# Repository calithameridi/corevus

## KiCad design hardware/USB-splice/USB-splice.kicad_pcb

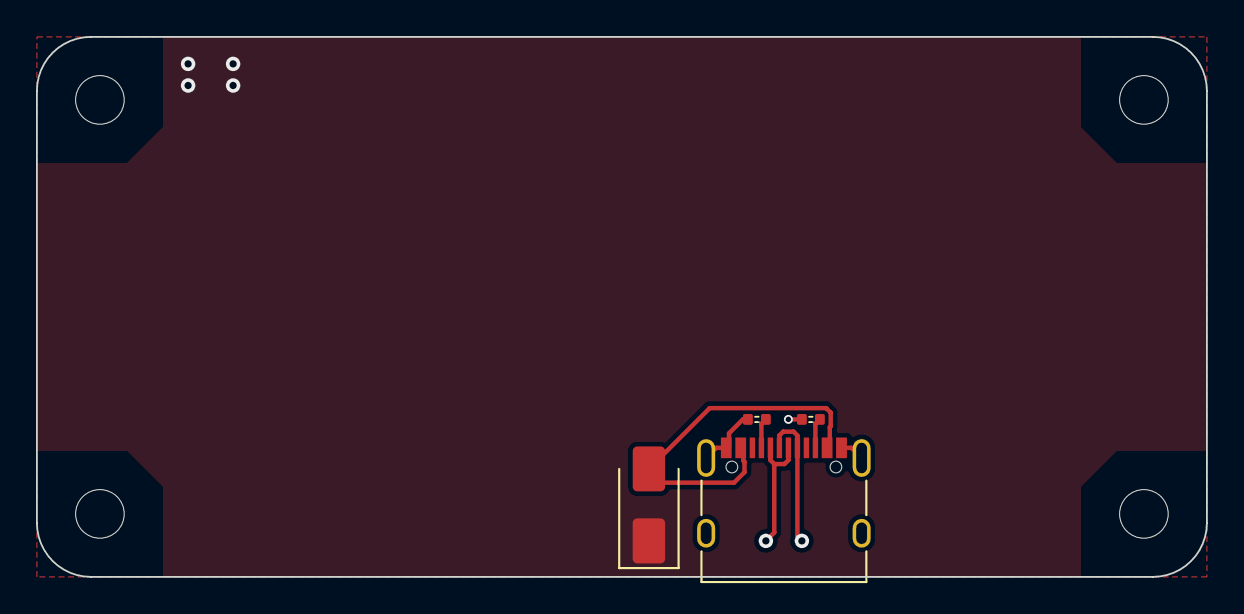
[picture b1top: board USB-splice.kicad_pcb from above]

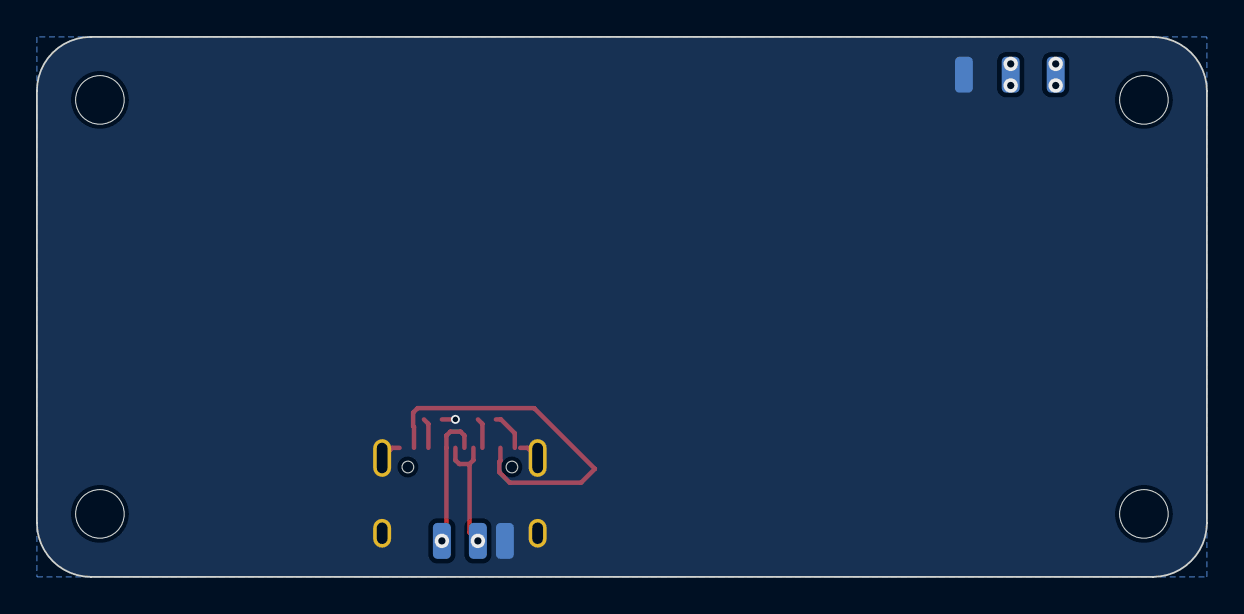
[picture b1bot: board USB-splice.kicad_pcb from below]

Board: 2 copper layers, 65.0 x 30.0 mm, 14 parts (6 on the bottom side), 7 nets.

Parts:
D1: SS54; D_SMA
H1, H2, H3, H4: MountingHole; MountingHole_2.7mm_M2.5
J1: USB 2.0; USB_Type-C_16p
R1, R2: 5.1kΩ; 0402R
T1, T2: 5V; LGA_Land_2mm
T3, T6: Gnd; LGA_Land_2mm
T4: D-; LGA_Land_2mm
T5: D+; LGA_Land_2mm

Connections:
+5V: D1.1 (K), T1.1, T2.1
GND: J1.A1 (GND), J1.A12 (GND), J1.B1 (GND), J1.B12 (GND), J1.S1 (SHIELD), R1.1, R2.1, T3.1, T6.1
unnamed: D1.2 (A), J1.A4 (VBUS), J1.A9 (VBUS), J1.B4 (VBUS), J1.B9 (VBUS)
unnamed: J1.A5 (CC1), R1.2
unnamed: J1.B5 (CC2), R2.2
unnamed: J1.A6 (D+), J1.B6 (D+), T5.1
unnamed: J1.A7 (D-), J1.B7 (D-), T4.1

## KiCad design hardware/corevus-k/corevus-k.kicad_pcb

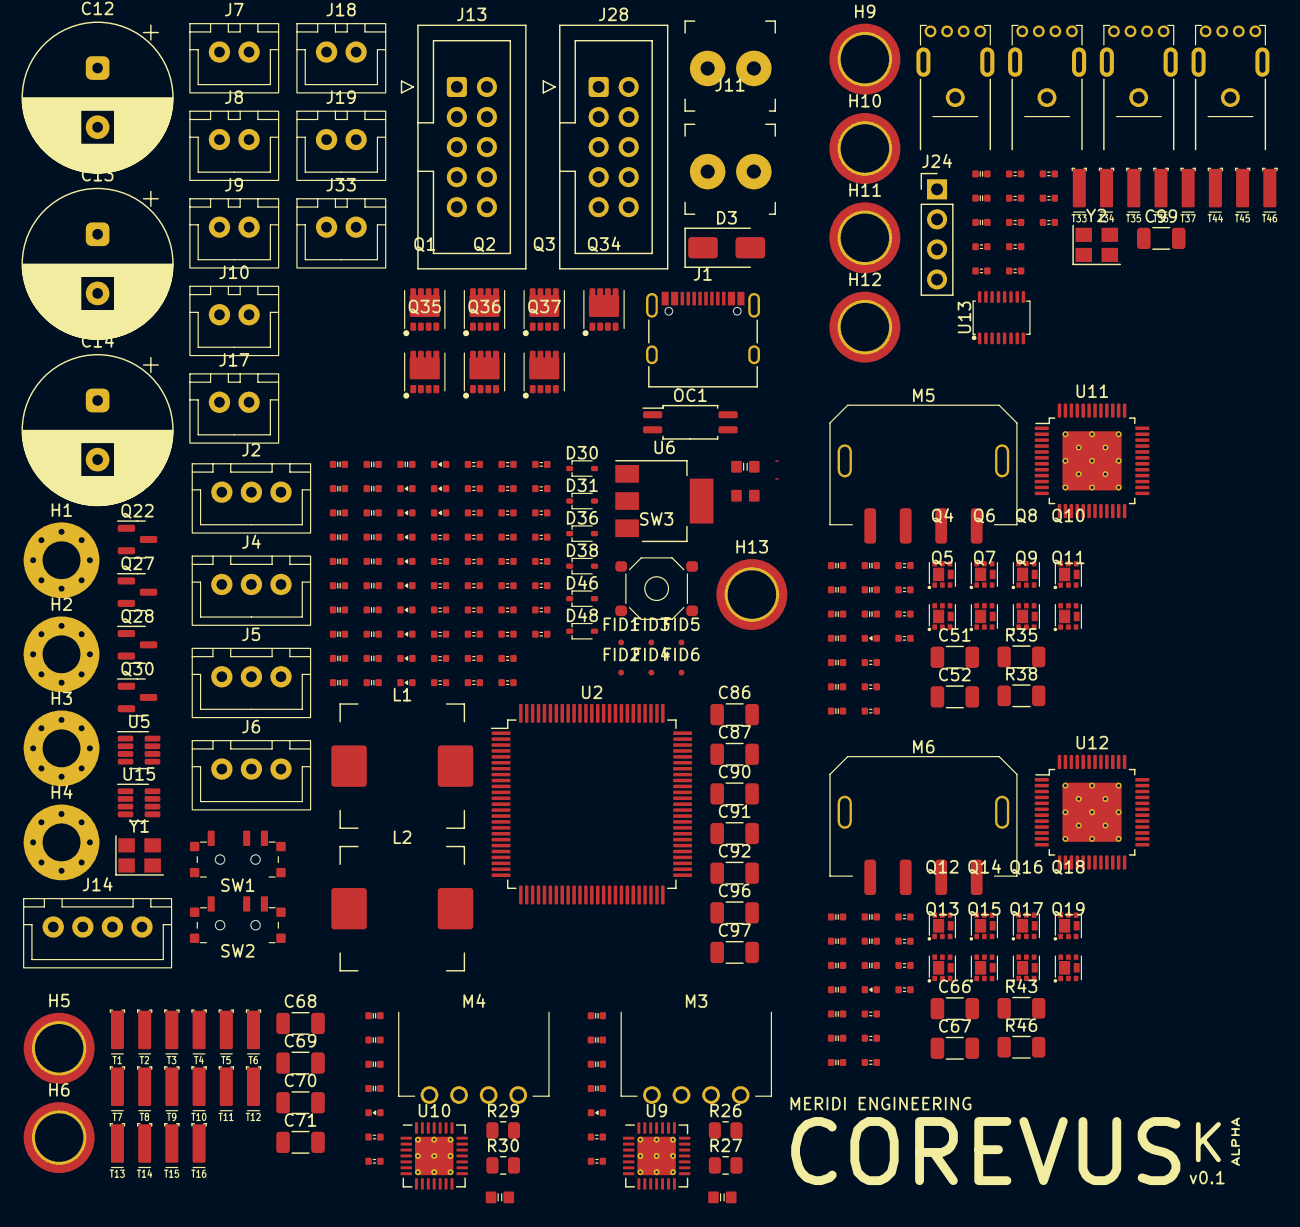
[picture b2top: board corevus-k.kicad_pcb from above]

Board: 4 copper layers, 283 parts (0 on the bottom side), 186 nets, no tracks yet.

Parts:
C1, C2: 15pF; 0402C
C3, C4: 2.2μF; 0402C
C5: 100nF 50V; 0402C
C6, C7, C8, C9, C29, C34, C41, C42, C43, C45, C56, C57, C58, C60, C76, C88, C93, C94, C98: 1μF; 0402C
C11: 10μF; 0603C
C12, C13, C14: 470μF 63V; CP_Radial_D12.5mm_P5.00mm
C28, C33, C38, C79, C80, C81, C82, C83, C84, C85, C89, C95: 100nF; 0402C
C30, C35, C39, C54: 100nF 16V; 0402C
C31, C36: 22nF 50V; 0402C
C32, C37: 1μF 50V; 0603C
C40, C55: 47nF 100V; 0402C
C47, C48, C49, C50, C62, C63, C64, C65: 220nF; 0402C
C51, C52, C66, C67: 1μF 100V; C_1206_3216Metric
C68, C69, C70, C71: 1μF 63V; C_1206_3216Metric
C86, C87, C92: 10μF 50V; C_1206_3216Metric
C90, C91: 22μF 25V; C_1206_3216Metric
C96, C97: 22μF 10V; C_1206_3216Metric
C99: 22μF; C_1206_3216Metric
D1, D2, D4, D5, D6, D7, D8, D19, D20, D23, D24, D28, D29, D32, D34, D49: Red; 0402LED
D3: SS54; D_SMA
D30, D31, D36, D38: 1N4148; D_SOD-323
D46, D48: 1N5819; D_SOD-323
FB1: GZ1608; 0603
FID1, FID2, FID3, FID4, FID5, FID6: Fiducial; Fiducial_0.5mm_Mask1mm
H1, H2, H3, H4: MountingHole; MountingHole_3.2mm_M3_Pad_Via
H5: V_{M}; M3_M2.5_PCB_Nut
H6: Gnd; M3_M2.5_PCB_Nut
H9, H10, H11, H12: M2.5; M3_M2.5_PCB_Nut
H13: Back; M3_M2.5_PCB_Nut
J1: USB 2.0; USB_Type-C_16p
J2: JST XH; JST_XH_1x03
J3, J11: ScrewTerminal; DB125-3.81-2P
J4, J5, J6: XH; JST_XH_1x03
J7, J8, J9, J10, J17, J18, J19, J33: JST XH; JST_XH_1x02
J12, J15, J16, J20: USB_A; Jing_USB-A_906-761
J13: EXP1; IDC-Header_2x05_P2.54mm_Vertical
J14: JST XH; JST_XH_1x04
J24: Conn_01x05_Pin; PinHeader_1x04_P2.54mm_Vertical
J28: EXP2; IDC-Header_2x05_P2.54mm_Vertical
L1, L2: 10μH; CJiang_FXL1040
M3, M4: JST XH; JST_XH_1x04-Side
M5, M6: Micro-Fit 3.0; XKB_X3025WRS-04C
NT1, NT2: NetTie_2; NetTie-2_SMD_Pad0.1mm
OC1: PC3H7; SOP-4_4.4x2.6mm_P1.27mm
Q1, Q2, Q3, Q34, Q35, Q36, Q37: 60N03F; MOSFET_DFN8
Q4, Q5, Q6, Q7, Q8, Q9, Q10, Q11, Q12, Q13, Q14, Q15, Q16, Q17, Q18, Q19: DMT6016LFDF
Q22, Q27, Q28, Q30: AO3400; SOT-23
R1, R19, R67, R71, R72, R73, R83, R102, R105, R106, R107: 10kΩ; 0402R
R2, R10, R12, R13, R14, R96, R98, R99, R101, R103: 1kΩ; 0402R
R4, R5, R69, R70, R75, R76, R77, R78, R79, R80, R81, R82: 33Ω; 0402R
R6, R7: 5.1kΩ; 0402R
R9: 200kΩ; 0402R
R11: 100kΩ; 0402R
R15, R16, R17, R18, R39, R47, R48, R49, R54, R93: 4.7kΩ; 0402R
R26, R27, R29, R30: 100mΩ; R_0805_2012Metric
R32, R40: 2.2Ω; 0402R
R33, R34, R36, R37, R41, R42, R44, R45: 47Ω; 0402R
R35, R38, R43, R46: 33mΩ; R_1206_3216Metric
R52, R55, R104: 200Ω; 0402R
R92: 330Ω; 0402R
R94: 1.5kΩ; 0402R
R95: 8.2kΩ; 0402R
SW1, SW2: SW_SPDT; MSS12C02-LS
SW3: SPST; XKB_TS-1187A
T1: V_{SA}; LGA_Spring
T2: SClk; LGA_Spring
T3, T35: Gnd; LGA_Spring
T4: MOSI; LGA_Spring
T5: MISO; LGA_Spring
T6: V_{CC}IO; LGA_Spring
T7, T8, T9, T10, T11, T12, T13, T14, T15, T16: TestPoint; LGA_Spring
T33, T34: 5V; LGA_Spring
T36: TXD; LGA_Spring
T37: RXD; LGA_Spring
T44: Shield; LGA_Spring
T45: D+; LGA_Spring
T46: D-; LGA_Spring
U2: STM32F407VETx; LQFP-100_14x14mm_P0.5mm
U5, U15: RT8110B; TSOT-23-8
U6: AMS1117-3.3; SOT-223-3_TabPin2
U9, U10: TMC2208-LA; TMC220x
U11, U12: TMC5160A-TA; TMCx160
U13: SL2.1S
Y1: 12 MHz; Crystal_SMD_3225-4Pin_3.2x2.5mm
Y2: 12MHz; Crystal_SMD_3225-4Pin_3.2x2.5mm

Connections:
+3.3V: C11.1, C28.1, C33.1, C41.2, C56.2, C79.1, C80.1, C81.1, C82.1, C83.1, C84.1, C85.1, D19.2 (A), D20.2 (A), D23.2 (A), D24.2 (A), FB1.1, J4.3, J5.3, J6.3, R12.2, R19.1, R52.2, R55.2, R102.1, R104.2, R105.1, R106.1, R107.1, SW1.3 (C), T6.1, U2.6 (VBAT), U2.11 (VDD), U2.19 (VDD), U2.28 (VDD), U2.50 (VDD), U2.75 (VDD), U2.100 (VDD), U6.2 (VO), U9.9 (MS1), U9.10 (MS2), U9.15 (Vcc_IO), U10.9 (MS1), U10.10 (MS2), U10.15 (Vcc_IO), U11.20 (VCC_IO), U11.21 (SD_MODE), U11.22 (SPI_MODE), U12.20 (VCC_IO), U12.21 (SD_MODE), U12.22 (SPI_MODE)
+5V: C96.1, C97.1, C98.1, C99.1, D3.1 (K), J12.1 (VBUS), J13.10, J15.1 (VBUS), J16.1 (VBUS), J20.1 (VBUS), J24.1, J28.10, L2.2, R95.2, SW2.3 (C), T33.1, T34.1, U6.3 (VI), U13.7 (VDD5)
+12V: C45.2, C60.2, C90.1, C91.1, L1.2, R93.2, T1.1, U11.3 (12VOUT), U11.4 (VSA), U12.3 (12VOUT), U12.4 (VSA)
+24V: C12.1, C30.2, C32.2, C35.2, C37.2, C68.1, C69.1, C70.1, C71.1, C86.1, C87.1, C92.1, H5.1, J3.1, J11.1, Q35.5 (D), Q35.6 (D), Q35.7 (D), Q35.8 (D), Q37.5 (D), Q37.6 (D), Q37.7 (D), Q37.8 (D), SW2.1 (A), U5.7 (VIN), U9.22 (VS), U9.28 (VS), U10.22 (VS), U10.28 (VS), U15.7 (VIN)
/BOOT0: D1.2 (A), R1.1, SW1.2 (B), U2.94 (BOOT0)
/E0: D6.1 (K), J4.1
/E1: D7.1 (K), J5.1
/E2: D8.1 (K), J6.1
/F0: D5.2 (A), J14.4, R67.1
/F1_V+: D38.1 (K), J33.1
/F2_Gate: D28.2 (A), Q22.1 (G), R71.1
/F2_V+: D30.1 (K), J17.1
/F3_Gate: D29.2 (A), Q27.1 (G), R72.1
/F3_V+: D31.1 (K), J18.1
/F4_Gate: D32.2 (A), Q28.1 (G), R73.1
/F4_V+: D36.1 (K), J19.1
/F6_Gate: D34.2 (A), Q30.1 (G), R83.1
/H0_Gate: D4.2 (A), Q3.4 (G)
/HB_Gate: D2.2 (A), Q1.4 (G), Q2.4 (G)
/Motor 0 (TMCx160)/CA1: C47.1, U11.42 (CA1)
/Motor 0 (TMCx160)/CA2: C49.2, U11.35 (CA2)
/Motor 0 (TMCx160)/CB1: C48.1, U11.2 (CB1)
/Motor 0 (TMCx160)/CB2: C50.2, U11.43 (CB2)
/Motor 0 (TMCx160)/HA1: Q6.3 (G), U11.41 (HA1)
/Motor 0 (TMCx160)/HA2: Q4.3 (G), U11.36 (HA2)
/Motor 0 (TMCx160)/HB1: Q10.3 (G), U11.1 (HB1)
/Motor 0 (TMCx160)/HB2: Q8.3 (G), U11.44 (HB2)
/Motor 0 (TMCx160)/LA1: Q7.3 (G), U11.39 (LA1)
/Motor 0 (TMCx160)/LA2: Q5.3 (G), U11.38 (LA2)
/Motor 0 (TMCx160)/LB1: Q11.3 (G), U11.47 (LB1)
/Motor 0 (TMCx160)/LB2: Q9.3 (G), U11.46 (LB2)
/Motor 0 (TMCx160)/Motor_A1: C47.2, M5.3, Q6.4 (S), Q6.7 (S), Q7.1 (D), Q7.2 (D), Q7.5 (D), Q7.6 (D), Q7.8 (D), U11.40 (BMA1)
/Motor 0 (TMCx160)/Motor_A2: C49.1, M5.4, Q4.4 (S), Q4.7 (S), Q5.1 (D), Q5.2 (D), Q5.5 (D), Q5.6 (D), Q5.8 (D), U11.37 (BMA2)
/Motor 0 (TMCx160)/Motor_B1: C48.2, M5.1, Q10.4 (S), Q10.7 (S), Q11.1 (D), Q11.2 (D), Q11.5 (D), Q11.6 (D), Q11.8 (D), U11.48 (BMB1)
/Motor 0 (TMCx160)/Motor_B2: C50.1, M5.2 (-), Q8.4 (S), Q8.7 (S), Q9.1 (D), Q9.2 (D), Q9.5 (D), Q9.6 (D), Q9.8 (D), U11.45 (BMB2)
/Motor 0 (TMCx160)/SRAH: R33.2, U11.8 (SRAH)
/Motor 0 (TMCx160)/SRAL: R34.2, U11.7 (SRAL)
/Motor 0 (TMCx160)/SRBH: R36.2, U11.9 (SRBH)
/Motor 0 (TMCx160)/SRBL: R37.2, U11.10 (SRBL)
/Motor 1 (TMCx160)/CA1: C62.1, U12.42 (CA1)
/Motor 1 (TMCx160)/CA2: C64.2, U12.35 (CA2)
/Motor 1 (TMCx160)/CB1: C63.1, U12.2 (CB1)
/Motor 1 (TMCx160)/CB2: C65.2, U12.43 (CB2)
/Motor 1 (TMCx160)/HA1: Q14.3 (G), U12.41 (HA1)
/Motor 1 (TMCx160)/HA2: Q12.3 (G), U12.36 (HA2)
/Motor 1 (TMCx160)/HB1: Q18.3 (G), U12.1 (HB1)
/Motor 1 (TMCx160)/HB2: Q16.3 (G), U12.44 (HB2)
/Motor 1 (TMCx160)/LA1: Q15.3 (G), U12.39 (LA1)
/Motor 1 (TMCx160)/LA2: Q13.3 (G), U12.38 (LA2)
/Motor 1 (TMCx160)/LB1: Q19.3 (G), U12.47 (LB1)
/Motor 1 (TMCx160)/LB2: Q17.3 (G), U12.46 (LB2)
/Motor 1 (TMCx160)/Motor_A1: C62.2, M6.3, Q14.4 (S), Q14.7 (S), Q15.1 (D), Q15.2 (D), Q15.5 (D), Q15.6 (D), Q15.8 (D), U12.40 (BMA1)
/Motor 1 (TMCx160)/Motor_A2: C64.1, M6.4, Q12.4 (S), Q12.7 (S), Q13.1 (D), Q13.2 (D), Q13.5 (D), Q13.6 (D), Q13.8 (D), U12.37 (BMA2)
/Motor 1 (TMCx160)/Motor_B1: C63.2, M6.1, Q18.4 (S), Q18.7 (S), Q19.1 (D), Q19.2 (D), Q19.5 (D), Q19.6 (D), Q19.8 (D), U12.48 (BMB1)
/Motor 1 (TMCx160)/Motor_B2: C65.1, M6.2 (-), Q16.4 (S), Q16.7 (S), Q17.1 (D), Q17.2 (D), Q17.5 (D), Q17.6 (D), Q17.8 (D), U12.45 (BMB2)
/Motor 1 (TMCx160)/SRAH: R41.2, U12.8 (SRAH)
/Motor 1 (TMCx160)/SRAL: R42.2, U12.7 (SRAL)
/Motor 1 (TMCx160)/SRBH: R44.2, U12.9 (SRBH)
/Motor 1 (TMCx160)/SRBL: R45.2, U12.10 (SRBL)
/Motor 2 (TMC2208)/A1: M3.2 (-), U9.24 (OA1)
/Motor 2 (TMC2208)/A2: M3.1, U9.21 (OA2)
/Motor 2 (TMC2208)/B1: M3.3, U9.26 (OB1)
/Motor 2 (TMC2208)/B2: M3.4, U9.1 (OB2)
/Motor 2 (TMC2208)/BRA: R26.1, U9.23 (BRA)
/Motor 2 (TMC2208)/BRB: R27.1, U9.27 (BRB)
/Motor 3 (TMC2208)/A1: M4.2 (-), U10.24 (OA1)
/Motor 3 (TMC2208)/A2: M4.1, U10.21 (OA2)
/Motor 3 (TMC2208)/B1: M4.3, U10.26 (OB1)
/Motor 3 (TMC2208)/B2: M4.4, U10.1 (OB2)
/Motor 3 (TMC2208)/BRA: R29.1, U10.23 (BRA)
/Motor 3 (TMC2208)/BRB: R30.1, U10.27 (BRB)
/Pi Zero + USB Hub/D1+: R75.2, U13.4 (DP1)
/Pi Zero + USB Hub/D1+': J12.3 (D+), R75.1
/Pi Zero + USB Hub/D1-: R76.2, U13.3 (DM1)
/Pi Zero + USB Hub/D1-': J12.2 (D-), R76.1
/Pi Zero + USB Hub/D2+: R77.2, U13.2 (DP2)
/Pi Zero + USB Hub/D2+': J15.3 (D+), R77.1
/Pi Zero + USB Hub/D2-: R78.2, U13.1 (DM2)
/Pi Zero + USB Hub/D2-': J15.2 (D-), R78.1
/Pi Zero + USB Hub/D3+: R79.2, U13.16 (DP3)
/Pi Zero + USB Hub/D3+': J16.3 (D+), R79.1
/Pi Zero + USB Hub/D3-: R80.2, U13.15 (DM3)
/Pi Zero + USB Hub/D3-': J16.2 (D-), R80.1
/Pi Zero + USB Hub/D4+: R81.2, U13.14 (DP4)
/Pi Zero + USB Hub/D4+': J20.3 (D+), R81.1
/Pi Zero + USB Hub/D4-: R82.2, U13.13 (DM4)
/Pi Zero + USB Hub/D4-': J20.2 (D-), R82.1
/Pi Zero + USB Hub/DU+: R69.1, U13.6 (UDP)
/Pi Zero + USB Hub/DU+': R69.2, T45.1
/Pi Zero + USB Hub/DU-: R70.1, U13.5 (UDM)
/Pi Zero + USB Hub/DU-': R70.2, T46.1
/Probe: OC1.3, R11.1, R96.2
/SPI1_MISO: T5.1, U11.16 (SDO/CFG0), U12.16 (SDO/CFG0)
/SPI1_MOSI: T4.1, U11.15 (SDI/CFG1), U12.15 (SDI/CFG1)
/SPI1_SCK: T2.1, U11.14 (SCK/CFG2), U12.14 (SCK/CFG2)
/T0: C6.2, J8.2, R15.1
/T1: C7.2, J7.2, R16.1
/T2: C8.2, J9.2, R17.1
/T3: C9.2, J10.2, R18.1
/USART2_RX: J24.3, T36.1
/USART2_TX: J24.4, T37.1
/_{M0}~En: R99.2, R107.2, U12.28 (~DRV_EN)
/_{M2}~En: R101.2, R102.2, U9.2 (~En)
/_{M3}~En: R103.2, R105.2, U10.2 (~En)
/_{M4}~En: R98.2, R106.2, U11.28 (~DRV_EN)
GND: C1.1, C2.1, C3.2, C4.2, C5.2, C11.2, C12.2, C13.2, C14.2, C28.2, C29.1, C32.1, C33.2, C34.1, C37.1, C38.2, C41.1, C42.1, C43.1, C45.1, C51.2, C52.2, C56.1, C57.1, C58.1, C60.1, C66.2, C67.2, C68.2, C69.2, C70.2, C71.2, C76.2, C79.2, C80.2, C81.2, C82.2, C83.2, C84.2, C85.2, C86.2, C87.2, C88.2, C90.2, C91.2, C92.2, C93.2, C94.2, C96.2, C97.2, C98.2, C99.2, D49.1 (K), H6.1, H9.1, H10.1, H11.1, H12.1, J1.A1 (GND), J1.A12 (GND), J1.B1 (GND), J1.B12 (GND), J1.S1 (SHIELD), J2.2, J4.2, J5.2, J6.2, J12.4 (GND), J12.5 (Shield), J13.9, J14.2, J15.4 (GND), J15.5 (Shield), J16.4 (GND), J16.5 (Shield), J20.4 (GND), J20.5 (Shield), J24.2, J28.9, NT1.1, OC1.2, Q1.1 (S), Q1.2 (S), Q1.3 (S), Q2.1 (S), Q2.2 (S), Q2.3 (S), Q3.1 (S), Q3.2 (S), Q3.3 (S), Q22.2 (S), Q27.2 (S), Q28.2 (S), Q30.2 (S), Q34.1 (S), Q34.2 (S), Q34.3 (S), Q36.1 (S), Q36.2 (S), Q36.3 (S), R1.2, R2.1, R6.1, R7.1, R9.2, R11.2, R13.2, R14.2, R26.2, R27.2, R29.2, R30.2, R34.1, R35.2, R37.1, R38.2, R39.2, R42.1, R43.2, R45.1, R46.2, R47.2, R48.2, R49.2, R54.2, R67.2, R71.2, R72.2, R73.2, R83.2, R92.2, R94.2, SW1.1 (A), SW3.1, T3.1, T9.1, T10.1, T35.1, T44.1, U2.10 (VSS), U2.27 (VSS), U2.74 (VSS), U2.99 (VSS), U5.3 (GND), U6.1 (GND), U9.3 (Gnd), U9.7 (NC), U9.18 (Gnd), U9.20 (NC), U9.25 (NC), U9.29 (Pad), U10.3 (Gnd), U10.7 (NC), U10.18 (Gnd), U10.20 (NC), U10.25 (NC), U10.29 (Pad), U11.6 (GNDA), U11.11 (TST_MODE), U11.12 (CLK), U11.19 (GNDD), U11.30 (GNDD), U11.49 (EP), U12.6 (GNDA), U12.11 (TST_MODE), U12.12 (CLK), U12.19 (GNDD), U12.30 (GNDD), U12.49 (EP), U13.8 (VSS), U15.3 (GND), Y1.2, Y1.4, Y2.2, Y2.4
unnamed: D1.1 (K), R2.2
unnamed: D2.1 (K), R13.1
unnamed: D3.2 (A), J1.A4 (VBUS), J1.A9 (VBUS), J1.B4 (VBUS), J1.B9 (VBUS)
unnamed: D4.1 (K), R14.1
unnamed: D5.1 (K), R49.1
unnamed: D6.2 (A), R52.1
unnamed: D7.2 (A), R55.1
unnamed: D8.2 (A), R104.1
unnamed: D19.1 (K), R98.1
unnamed: D20.1 (K), R99.1
unnamed: D23.1 (K), R101.1
unnamed: D24.1 (K), R103.1
unnamed: D28.1 (K), R39.1
unnamed: D29.1 (K), R47.1
unnamed: D30.2 (A), J17.2, Q22.3 (D)
unnamed: D31.2 (A), J18.2, Q27.3 (D)
unnamed: D32.1 (K), R48.1
unnamed: D34.1 (K), R54.1
unnamed: D36.2 (A), J19.2, Q28.3 (D)
unnamed: D38.2 (A), J33.2, Q30.3 (D)
unnamed: C88.1, D46.2 (A), U15.1 (VCC)
unnamed: C89.1, D46.1 (K), U15.5 (BOOT)
unnamed: C94.1, D48.2 (A), U5.1 (VCC)
unnamed: C95.1, D48.1 (K), U5.5 (BOOT)
unnamed: D49.2 (A), R96.1
unnamed: J1.A5 (CC1), R6.2
unnamed: J1.B5 (CC2), R7.2
unnamed: J1.A6 (D+), J1.B6 (D+), R5.2
unnamed: J1.A7 (D-), J1.B7 (D-), R4.2
unnamed: C5.1, J2.1, SW2.2 (B)
unnamed: J2.3, R10.1
unnamed: J3.2, Q3.5 (D), Q3.6 (D), Q3.7 (D), Q3.8 (D)
unnamed: J11.2, Q1.5 (D), Q1.6 (D), Q1.7 (D), Q1.8 (D), Q2.5 (D), Q2.6 (D), Q2.7 (D), Q2.8 (D)
unnamed: OC1.1, R10.2
unnamed: OC1.4, R12.1
unnamed: Q5.4 (S), Q5.7 (S), Q7.4 (S), Q7.7 (S), R33.1, R35.1
unnamed: Q9.4 (S), Q9.7 (S), Q11.4 (S), Q11.7 (S), R36.1, R38.1
unnamed: Q13.4 (S), Q13.7 (S), Q15.4 (S), Q15.7 (S), R41.1, R43.1
unnamed: Q17.4 (S), Q17.7 (S), Q19.4 (S), Q19.7 (S), R44.1, R46.1
unnamed: Q34.4 (G), U15.2 (LGATE)
unnamed: Q35.4 (G), U15.4 (UGATE)
unnamed: Q36.4 (G), U5.2 (LGATE)
unnamed: Q37.4 (G), U5.4 (UGATE)
unnamed: C38.1, R19.2, SW3.2, U2.14 (NRST)
unnamed: R4.1, U2.70 (PA11)
unnamed: R5.1, U2.71 (PA12)
unnamed: C1.2, U2.12 (PH0), Y1.1
unnamed: C2.2, U2.13 (PH1), Y1.3
unnamed: C4.1, U2.49 (VCAP_1)
unnamed: C3.1, U2.73 (VCAP_2)
unnamed: NT2.2, U2.21 (VREF+)
unnamed: R94.1, R95.1, U5.8 (FB)
unnamed: C95.2, L2.1, Q36.5 (D), Q36.6 (D), Q36.7 (D), Q36.8 (D), Q37.1 (S), Q37.2 (S), Q37.3 (S), U5.6 (PHASE)
unnamed: C29.2, U9.8 (5VOut)
unnamed: C31.2, U9.5 (CPI)
unnamed: C31.1, U9.4 (CPO)
unnamed: C30.1, U9.6 (VCP)
unnamed: C34.2, U10.8 (5VOut)
unnamed: C36.2, U10.5 (CPI)
unnamed: C36.1, U10.4 (CPO)
unnamed: C35.1, U10.6 (VCP)
unnamed: C42.2, R32.1, U11.5 (5VOUT)
unnamed: C40.1, U11.32 (CPI)
unnamed: C40.2, U11.31 (CPO)
unnamed: C43.2, R32.2, U11.29 (VCC)
unnamed: C39.1, U11.34 (VCP)
unnamed: C57.2, R40.1, U12.5 (5VOUT)
unnamed: C55.1, U12.32 (CPI)
unnamed: C55.2, U12.31 (CPO)
unnamed: C58.2, R40.2, U12.29 (VCC)
unnamed: C54.1, U12.34 (VCP)
unnamed: C76.1, U13.10 (VDD18)
unnamed: C93.1, U13.9 (VDD33)
unnamed: U13.12 (XIN), Y2.1
unnamed: U13.11 (XOUT), Y2.3
unnamed: R92.1, R93.1, U15.8 (FB)
unnamed: C89.2, L1.1, Q34.5 (D), Q34.6 (D), Q34.7 (D), Q34.8 (D), Q35.1 (S), Q35.2 (S), Q35.3 (S), U15.6 (PHASE)
VDDA: FB1.2, NT2.1, R15.2, R16.2, R17.2, R18.2, U2.22 (VDDA)
VMB: C13.1, C14.1, C39.2, C51.1, C52.1, C54.2, C66.1, C67.1, Q4.1 (D), Q4.2 (D), Q4.5 (D), Q4.6 (D), Q4.8 (D), Q6.1 (D), Q6.2 (D), Q6.5 (D), Q6.6 (D), Q6.8 (D), Q8.1 (D), Q8.2 (D), Q8.5 (D), Q8.6 (D), Q8.8 (D), Q10.1 (D), Q10.2 (D), Q10.5 (D), Q10.6 (D), Q10.8 (D), Q12.1 (D), Q12.2 (D), Q12.5 (D), Q12.6 (D), Q12.8 (D), Q14.1 (D), Q14.2 (D), Q14.5 (D), Q14.6 (D), Q14.8 (D), Q16.1 (D), Q16.2 (D), Q16.5 (D), Q16.6 (D), Q16.8 (D), Q18.1 (D), Q18.2 (D), Q18.5 (D), Q18.6 (D), Q18.8 (D), R9.1, U11.33 (VS), U12.33 (VS)
VSSA: C6.1, C7.1, C8.1, C9.1, J7.1, J8.1, J9.1, J10.1, NT1.2, U2.20 (VSSA)

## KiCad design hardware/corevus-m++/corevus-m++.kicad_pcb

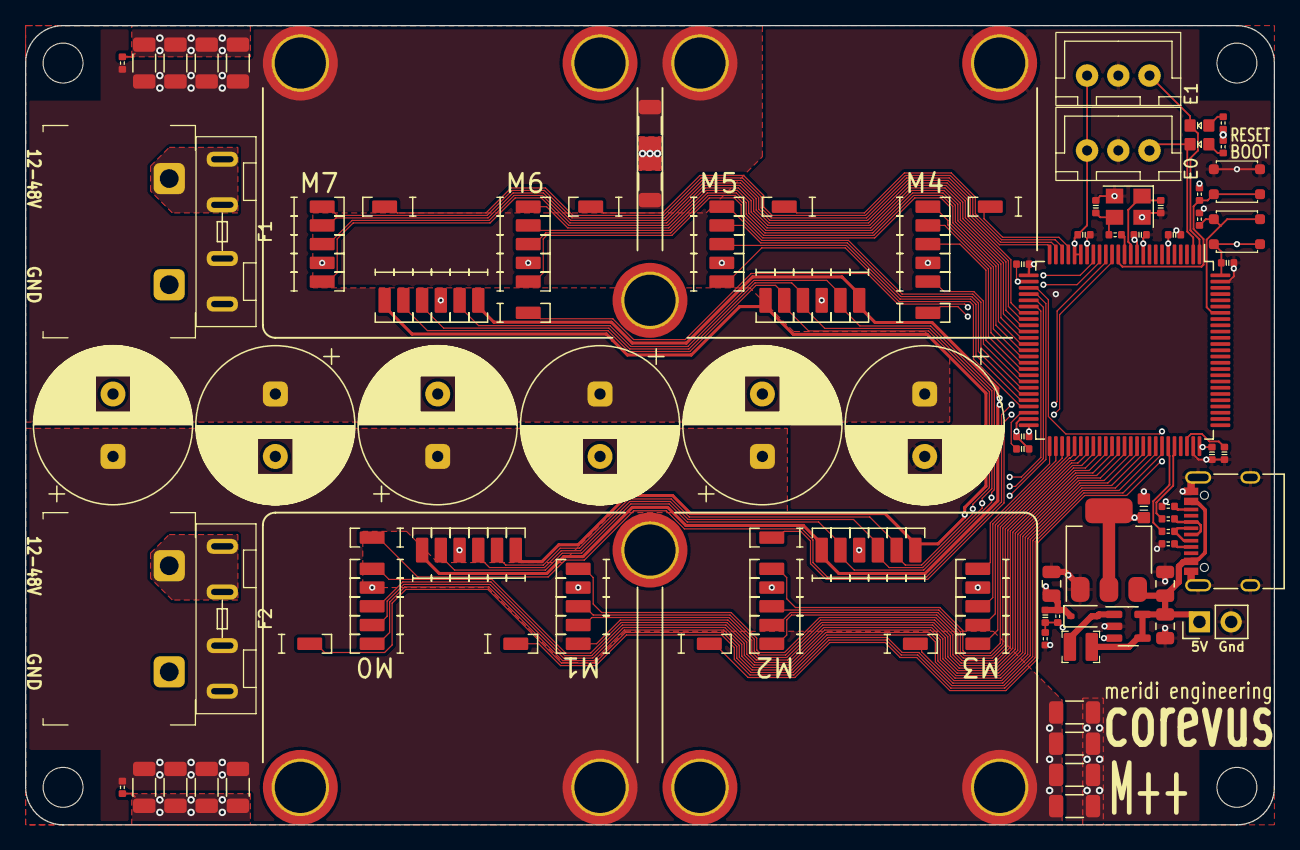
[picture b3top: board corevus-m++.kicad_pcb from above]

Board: 4 copper layers, 100.0 x 64.0 mm, 157 parts (0 on the bottom side), 74 nets.

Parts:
C1, C2, C7: 10μF; C_0805_2012Metric
C3, C4: 16pF; 0402C
C5: 10μF; 0603C
C6: 4.7pF; 0402C
C8, C9, C10, C33, C34, C35, C36, C37, C38: 1µF; 0402C
C11, C12, C13, C14, C15, C16: 390μF 63V; CP_Radial_D12.5mm_P5.00mm
C17, C19, C20, C21, C23, C24, C25, C26, C27, C28, C29, C30, C31, C32: 1μF 63V; C_1206_3216Metric
D1, D2: Red; 0603LED
D3: 5819; D_SOD-323
F1, F2: 10A; XF-506P
H1, H2, H3, H4: MountingHole; MountingHole_3.2mm_M3
H5, H6: Back; M3_M2.5_PCB_Nut
H7, H9, H11, H13: V_{M}; M3_M2.5_PCB_Nut
H8, H10, H12, H14: Gnd; M3_M2.5_PCB_Nut
J1, J2: XH; JST_XH_1x03
J3: USB 2.0; USB_Type-C_16p
J4, J5: Power In; Kefa_KF8500-8.5-2P
J6: 1x2P; PinHeader_1x02_P2.54mm_Vertical
L1: 10µH; L_Changjiang_FTC2520
R1, R2: 2.2kΩ; 0402R
R3, R5, R6: 10kΩ; 0402R
R4: 100kΩ; 0402R
R7, R8: 33Ω; 0402R
R9, R10: 5.1kΩ; 0402R
R11: 1kΩ; 0402R
R12, R13: 200kΩ; 0402R
SW1: RST; ShouHan_TS3315A
SW2: BOOT; ShouHan_TS3315A
T1, T8, T15, T22: V_{SA}; LGA_Spring
T2, T9, T16, T23: SClk; LGA_Spring
T3, T10, T17, T24: MOSI; LGA_Spring
T4, T11, T18, T25, T53, T54, T55, T56, T57, T58, T59, T60: Gnd; LGA_Spring
T5, T12, T19, T26: MISO; LGA_Spring
T6, T13, T20, T27: 3.3V; LGA_Spring
T7, T14, T21, T28: Therm; LGA_Spring
T29, T30, T31, T32, T33, T34, T35, T36: CS; LGA_Spring
T37, T38, T39, T40, T41, T42, T43, T44: En; LGA_Spring
T45, T46, T47, T48, T49, T50, T51, T52: Dir; LGA_Spring
T61, T62, T63, T64, T65, T66, T67, T68: Step; LGA_Spring
T69, T70, T71, T72, T73, T74, T75, T76: Stall; LGA_Spring
U1: AMS1117-3.3; SOT-223-3_TabPin2
U2: TPS61040DBV; SOT-23-5
U3: STM32H750VBTx; LQFP-100_14x14mm_P0.5mm
Y1: 25 MHz; Crystal_SMD_3225-4Pin_3.2x2.5mm

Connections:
+3.3V: C5.1, C8.1, C9.1, C10.1, C33.1, C34.1, C35.1, C38.1, J1.3, J2.3, R1.2, R2.2, R5.2, SW2.2, T6.1, T13.1, T20.1, T27.1, U1.2 (VO), U3.6 (VBAT), U3.11 (VDD), U3.20 (VREF+), U3.21 (VDDA), U3.27 (VDD), U3.50 (VDD), U3.75 (VDD), U3.100 (VDD)
+5V: C1.1, C2.1, J3.A4 (VBUS), J3.A9 (VBUS), J3.B4 (VBUS), J3.B9 (VBUS), J6.1, L1.1, U1.3 (VI), U2.4 (EN), U2.5 (VIN)
+12V: C6.2, C7.1, D3.1 (K), R4.1, T1.1, T8.1, T15.1, T22.1
/BOOT0: R6.1, SW2.1, U3.94 (BOOT0)
/E0: D1.1 (K), J1.1, U3.1 (PE2)
/E1: D2.1 (K), J2.1, U3.2 (PE3)
/MISO: T5.1, T12.1, T19.1, T26.1
/MOSI: T3.1, T10.1, T17.1, T24.1
/NRST: R5.1, SW1.2, U3.14 (NRST)
/SCK: T2.1, T9.1, T16.1, T23.1
/_{M0}Dir: T52.1, U3.64 (PC7)
/_{M0}Stall: T76.1, U3.68 (PA9)
/_{M0}Step: T68.1, U3.63 (PC6)
/_{M0}Th: T28.1, U3.16 (PC1)
/_{M0}~CS: T36.1, U3.66 (PC9)
/_{M0}~En: T44.1, U3.65 (PC8)
/_{M1}Dir: T51.1, U3.60 (PD13)
/_{M1}Stall: T75.1, U3.69 (PA10)
/_{M1}Step: T67.1, U3.59 (PD12)
/_{M1}~CS: T35.1, U3.62 (PD15)
/_{M1}~En: T43.1, U3.61 (PD14)
/_{M2}Dir: T50.1, U3.56 (PD9)
/_{M2}Stall: T74.1, U3.28 (PA4)
/_{M2}Step: T66.1, U3.55 (PD8)
/_{M2}Th: T21.1, U3.15 (PC0)
/_{M2}~CS: T34.1, U3.58 (PD11)
/_{M2}~En: T42.1, U3.57 (PD10)
/_{M3}Dir: T49.1, U3.52 (PB13)
/_{M3}Stall: T73.1, U3.67 (PA8)
/_{M3}Step: T65.1, U3.51 (PB12)
/_{M3}~CS: T33.1, U3.54 (PB15)
/_{M3}~En: T41.1, U3.53 (PB14)
/_{M4}Dir: T48.1, U3.42 (PE12)
/_{M4}Stall: T72.1, U3.22 (PA0)
/_{M4}Step: T64.1, U3.43 (PE13)
/_{M4}Th: T14.1, U3.17 (PC2_C)
/_{M4}~CS: T32.1, U3.40 (PE10)
/_{M4}~En: T40.1, U3.41 (PE11)
/_{M5}Dir: T47.1, U3.46 (PB10)
/_{M5}Stall: T71.1, U3.23 (PA1)
/_{M5}Step: T63.1, U3.47 (PB11)
/_{M5}~CS: T31.1, U3.44 (PE14)
/_{M5}~En: T39.1, U3.45 (PE15)
/_{M6}Dir: T46.1, U3.38 (PE8)
/_{M6}Stall: T70.1, U3.24 (PA2)
/_{M6}Step: T62.1, U3.39 (PE9)
/_{M6}Th: T7.1, U3.18 (PC3_C)
/_{M6}~CS: T30.1, U3.36 (PB2)
/_{M6}~En: T38.1, U3.37 (PE7)
/_{M7}Dir: T45.1, U3.34 (PB0)
/_{M7}Stall: T69.1, U3.25 (PA3)
/_{M7}Step: T61.1, U3.35 (PB1)
/_{M7}~CS: T29.1, U3.32 (PC4)
/_{M7}~En: T37.1, U3.33 (PC5)
GND: C1.2, C2.2, C3.1, C4.1, C5.2, C7.2, C8.2, C9.2, C10.2, C11.2, C12.2, C13.2, C14.2, C15.2, C16.2, C17.2, C19.2, C20.2, C21.2, C23.2, C24.2, C25.2, C26.2, C27.2, C28.2, C29.2, C30.2, C31.2, C32.2, C33.2, C34.2, C35.2, C36.1, C37.1, C38.2, H8.1, H10.1, H12.1, H14.1, J1.2, J2.2, J3.A1 (GND), J3.A12 (GND), J3.B1 (GND), J3.B12 (GND), J3.S1 (SHIELD), J4.2, J5.2, J6.2, R3.1, R6.2, R9.1, R10.1, R12.1, R13.1, SW1.1, T4.1, T11.1, T18.1, T25.1, T53.1, T54.1, T55.1, T56.1, T57.1, T58.1, T59.1, T60.1, U1.1 (GND), U2.2 (GND), U3.10 (VSS), U3.19 (VSSA), U3.26 (VSS), U3.49 (VSS), U3.74 (VSS), U3.99 (VSS), Y1.2, Y1.4
unnamed: C4.2, R11.1, Y1.3
unnamed: C36.2, U3.48 (VCAP)
unnamed: C37.2, U3.73 (VCAP)
unnamed: D1.2 (A), R1.1
unnamed: D2.2 (A), R2.1
unnamed: D3.2 (A), L1.2, U2.1 (SW)
unnamed: J3.A5 (CC1), R9.2
unnamed: J3.B5 (CC2), R10.2
unnamed: J3.A6 (D+), J3.B6 (D+), R8.1
unnamed: J3.A7 (D-), J3.B7 (D-), R7.1
unnamed: F1.1, J4.1
unnamed: F2.1, J5.1
unnamed: C6.1, R3.2, R4.2, U2.3 (FB)
unnamed: R7.2, U3.70 (PA11)
unnamed: R8.2, U3.71 (PA12)
unnamed: C3.2, U3.12 (PH0), Y1.1
unnamed: R11.2, U3.13 (PH1)
VMA: C11.1, C12.1, C13.1, C19.1, C20.1, C23.1, C24.1, C27.1, C28.1, C31.1, C32.1, F2.2, H11.1, H13.1, R13.2
VMB: C14.1, C15.1, C16.1, C17.1, C21.1, C25.1, C26.1, C29.1, C30.1, F1.2, H7.1, H9.1, R12.2

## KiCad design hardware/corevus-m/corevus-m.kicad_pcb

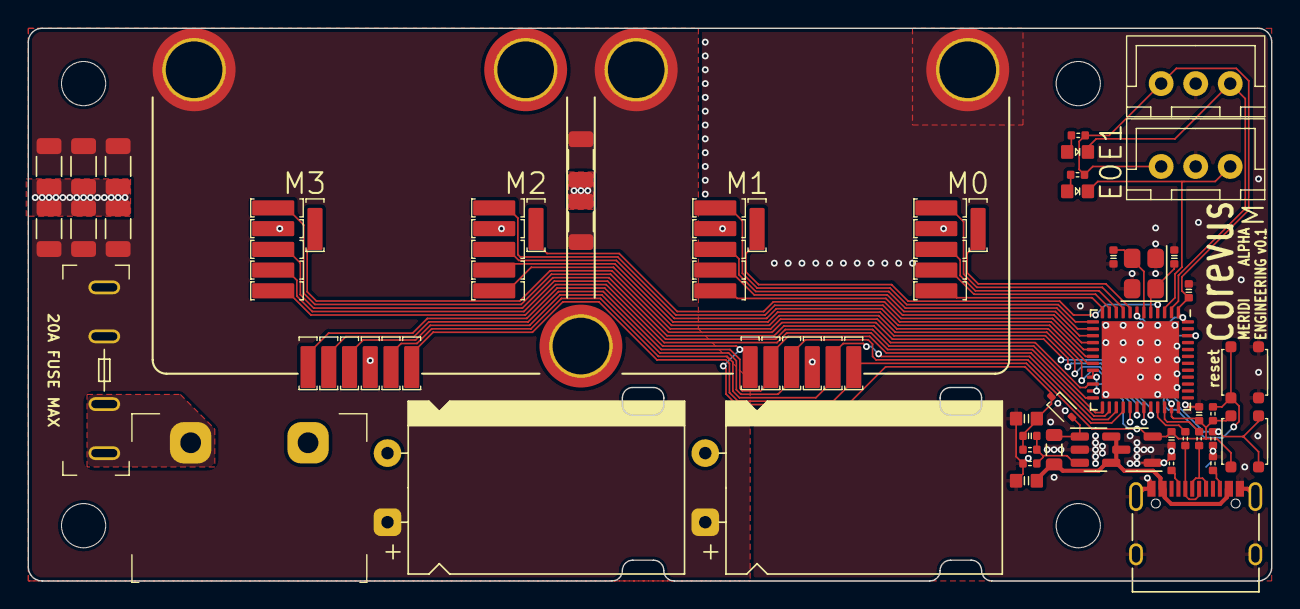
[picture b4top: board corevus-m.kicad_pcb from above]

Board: 2 copper layers, 90.0 x 40.0 mm, 88 parts (0 on the bottom side), 45 nets.

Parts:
C1, C2, C3: 1µF; 0402C
C7, C8: 15pF; 0402C
C11, C13: 10μF; 0603C
C12: 4.7pF; 0402C
C14, C15, C16, C17, C18, C19, C20, C21: 1μF 63V; C_1206_3216Metric
C22, C23: 680μF 63V; CP_Radial_D12.5mm_P5.00mm_H20mm_Horizontal
D1: 5819; D_SOD-323
D2, D3: Red; 0603LED
F1: 10A; XF-505P
H1, H3: V_{M}; M3_M2.5_PCB_Nut
H2, H4: Gnd; M3_M2.5_PCB_Nut
H5: Back; M3_M2.5_PCB_Nut
H6, H7, H8, H9: MountingHole; MountingHole_3.2mm_M3
J1: Power In; Kefa_KF8500-8.5-2P
J2: USB 2.0; USB_Type-C_16p
J3, J4: XH; JST_XH_1x03
L1: 10µH; L_0805_2012Metric
R1, R3, R7: 10kΩ; 0402R
R2, R4: 200Ω; 0402R
R8: 100kΩ; 0402R
R9, R10: 33Ω; 0402R
R11, R12: 5.1kΩ; 0402R
SW1: BOOT; ShouHan_TS3315A
SW2: RST; ShouHan_TS3315A
T1, T19: V_{SA}; LGA_Spring
T2, T20: SClk; LGA_Spring
T3, T21: MOSI; LGA_Spring
T4, T10, T16, T22, T28, T34: Gnd; LGA_Spring
T5, T23: MISO; LGA_Spring
T6, T24: 3.3V; LGA_Spring
T7, T13, T25, T31: CS; LGA_Spring
T8, T14, T26, T32: En; LGA_Spring
T9, T15, T27, T33: Dir; LGA_Spring
T11, T17, T29, T35: Step; LGA_Spring
T12, T18, T30, T36: Diag; LGA_Spring
U1: STM32G431CBUx; QFN-48-1EP_7x7mm_P0.5mm_EP5.6x5.6mm
U2: TPS61040DBV; SOT-23-5
U3: XC6206P332MR; SOT-23-3
Y1: 12 MHz; Crystal_SMD_3225-4Pin_3.2x2.5mm

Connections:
+3.3V: C1.1, C2.1, C3.1, J3.3, J4.3, R2.2, R3.1, R4.2, SW1.2, T6.1, T24.1, U1.1 (VBAT), U1.20 (VREF+), U1.21 (VDDA), U1.23 (VDD), U1.35 (VDD), U1.48 (VDD), U3.2 (VO)
+5V: C11.1, J2.A4 (VBUS), J2.A9 (VBUS), J2.B4 (VBUS), J2.B9 (VBUS), L1.1, U2.4 (EN), U2.5 (VIN), U3.3 (VI)
+12V: C12.2, C13.1, D1.1 (K), R8.1, T1.1, T19.1
+48V: C14.1, C15.1, C16.1, C17.1, C18.1, C19.1, C20.1, C21.1, C22.1, C23.1, F1.2, H1.1, H3.1
/BOOT0: R1.2, SW1.1, U1.46 (PB8)
/E0: D2.1 (K), J3.1, U1.2 (PC13)
/E1: D3.1 (K), J4.1, U1.3 (PC14)
/MISO: T5.1, T23.1, U1.27 (PB14)
/MOSI: T3.1, T21.1, U1.28 (PB15)
/SCK: T2.1, T20.1, U1.26 (PB13)
/_{M10}Diag: T12.1, U1.8 (PA0)
/_{M10}Dir: T9.1, U1.10 (PA2)
/_{M10}Step: T11.1, U1.9 (PA1)
/_{M10}~CS: T7.1, U1.12 (PA4)
/_{M10}~En: T8.1, U1.11 (PA3)
/_{M12}Diag: T18.1, U1.4 (PC15)
/_{M12}Dir: T15.1, U1.14 (PA6)
/_{M12}Step: T17.1, U1.13 (PA5)
/_{M12}~CS: T13.1, U1.16 (PC4)
/_{M12}~En: T14.1, U1.15 (PA7)
/_{M20}Diag: T30.1, U1.17 (PB0)
/_{M20}Dir: T27.1, U1.19 (PB2)
/_{M20}Step: T29.1, U1.18 (PB1)
/_{M20}~CS: T25.1, U1.30 (PA8)
/_{M20}~En: T26.1, U1.29 (PC6)
/_{M22}Diag: T36.1, U1.31 (PA9)
/_{M22}Dir: T33.1, U1.22 (PB10)
/_{M22}Step: T35.1, U1.32 (PA10)
/_{M22}~CS: T31.1, U1.25 (PB12)
/_{M22}~En: T32.1, U1.24 (PB11)
GND: C1.2, C2.2, C3.2, C7.1, C8.1, C11.2, C13.2, C14.2, C15.2, C16.2, C17.2, C18.2, C19.2, C20.2, C21.2, C22.2, C23.2, H2.1, H4.1, J1.2, J2.A1 (GND), J2.A12 (GND), J2.B1 (GND), J2.B12 (GND), J2.S1 (SHIELD), J3.2, J4.2, R1.1, R7.1, R11.1, R12.1, SW2.1, T4.1, T10.1, T16.1, T22.1, T28.1, T34.1, U1.49 (VSS), U2.2 (GND), U3.1 (GND), Y1.2, Y1.4
unnamed: D1.2 (A), L1.2, U2.1 (SW)
unnamed: D2.2 (A), R2.1
unnamed: D3.2 (A), R4.1
unnamed: F1.1, J1.1
unnamed: J2.A5 (CC1), R11.2
unnamed: J2.B5 (CC2), R12.2
unnamed: J2.A6 (D+), J2.B6 (D+), R10.1
unnamed: J2.A7 (D-), J2.B7 (D-), R9.1
unnamed: R9.2, U1.33 (PA11)
unnamed: R10.2, U1.34 (PA12)
unnamed: C7.2, U1.5 (PF0), Y1.1
unnamed: C8.2, U1.6 (PF1), Y1.3
unnamed: R3.2, SW2.2, U1.7 (PG10)
unnamed: C12.1, R7.2, R8.2, U2.3 (FB)

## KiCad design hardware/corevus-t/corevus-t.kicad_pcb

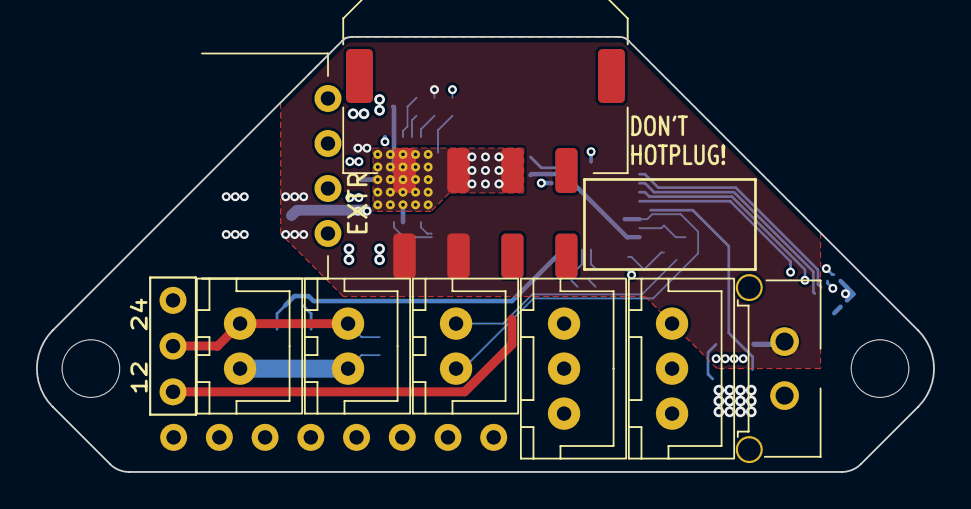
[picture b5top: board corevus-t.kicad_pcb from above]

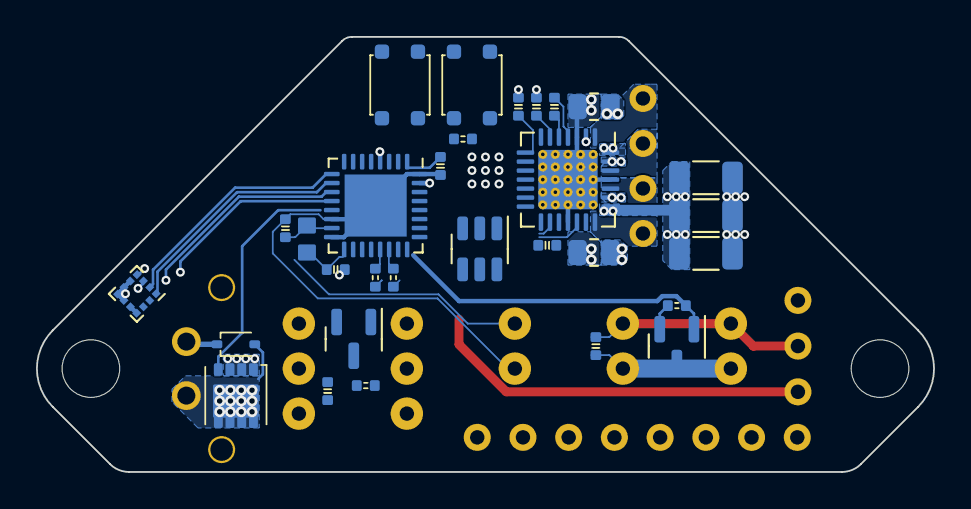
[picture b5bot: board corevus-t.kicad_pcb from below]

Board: 4 copper layers, 49.8 x 24.2 mm, 43 parts (31 on the bottom side), 33 nets.

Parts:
C1, C9: 100nF 50V; 0402C
C4, C5, C11, C12, C13: 1µF; 0402C
C6, C7, C14: 4.7µF 50V; C_1206_3216Metric
C8: 100nF 16V; 0402C
C10: 1μF; 0402C
D1: 5819; D_SOD-323
FB1: GZ1608; 0603
H1, H2: MountingHole; MountingHole_3.2mm_M3
J1: MF3; Molex_Micro-Fit-3.0_436500215
J2, J9: XH; JST_XH_1x03
J3: MF3; XKB_X3025WRS-2x04E
J4: XH; JST_XH_1x04-Side
J5, J6, J7: XH; JST_XH_1x02
J8: pinheader; PinHeader_1x08_P2.54mm_Vertical
J10: 1x3P; PinHeader_1x03_P2.54mm_Vertical
NT1: NetTie_2; NetTie-2_SMD_Pad0.1mm
Q1: AO3400; SOT-23
Q2: NMOS; MOSFET_DFN8
Q3: AO3401A; SOT-23
R1, R2, R7: 10kΩ; 0402R
R3, R4: 47Ω; 0402R
R5, R6: 100mΩ; R_0805_2012Metric
SW1: RST; ShouHan_TS3315A
SW2: BOOT; ShouHan_TS3315A
U1: LIS2DE12; LGA-12_2x2mm_P0.5mm
U2: TPS54302; SOT-23-6
U3: STM32G431KBU3; QFN-32-1EP_5x5mm_P0.5mm_EP3.45x3.45mm
U4: TMC2209-LA; TQFN-28-1EP_5x5mm_P0.5mm_EP3.25x3.25mm_ThermalVias

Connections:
+3.3V: C5.1, C11.1, C12.1, FB1.1, SW2.2, U1.9 (Vdd), U1.10 (Vdd_IO), U3.1 (VDD), U3.17 (VDD), U4.15 (VCC_IO)
+5V: J9.2, Q3.2 (S)
+12V: J3.7, J10.3, U2.3 (VIN)
+24V: C6.1, C7.1, C8.2, C14.1, D1.1 (K), J1.2, J3.5, J3.6, J10.1, U4.22 (VS), U4.28 (VS)
/A1: J4.3, U4.24 (OA1)
/A2: J4.4, U4.21 (OA2)
/ACCEL_CS: U1.2 (~CS), U3.9 (PA4)
/B1: J4.1, U4.1 (OB2)
/B2: J4.2, U4.26 (OB1)
/BOOT0: R2.2, SW2.1, U3.31 (PB8)
/F0_Gate: Q3.1 (G), R7.1
/F1_Gate: Q1.1 (G), R1.1
/F1_V+: C1.2, J6.2, J7.2, J10.2
/MISO: U1.3 (SA0/SDO), U3.11 (PA6)
/MOSI: U1.4 (SDA/SDI), U3.12 (PA7)
/SCK: U1.1 (SCL/SPC), U3.10 (PA5)
/USB_D+: R3.1, U3.22 (PA12)
/USB_D-: R4.1, U3.21 (PA11)
/~Reset: SW1.2, U3.4 (PG10)
GND: C4.2, C5.2, C6.2, C7.2, C10.1, C11.2, C12.2, C14.2, J2.1, J3.1, J3.2, J3.3, J9.1, NT1.1, Q1.2 (S), Q2.1 (S), Q2.2 (S), Q2.3 (S), R1.2, R2.1, R5.1, R6.1, R7.2, SW1.1, U1.5 (RES), U1.6 (GND), U1.7 (GND), U1.8 (GND), U2.1 (GND), U3.16 (VSS), U3.32 (VSS), U3.33 (VSS), U4.3 (GND), U4.18 (Gnd), U4.25 (NC), U4.29 (Pad)
unnamed: D1.2 (A), J1.1, Q2.5 (D), Q2.6 (D), Q2.7 (D), Q2.8 (D)
unnamed: C10.2, J2.2, Q3.3 (D)
unnamed: J3.4, R4.2
unnamed: J3.8, R3.2
unnamed: C1.1, J6.1, J7.1, Q1.3 (D)
unnamed: C13.1, FB1.2, U3.15 (VDDA)
unnamed: C4.1, U4.8 (5VOUT)
unnamed: R5.2, U4.23 (BRA)
unnamed: R6.2, U4.27 (BRB)
unnamed: C9.2, U4.5 (CPI)
unnamed: C9.1, U4.4 (CPO)
unnamed: C8.1, U4.6 (VCP)
VSSA: C13.2, J5.1, NT1.2, U3.14 (VSSA)
